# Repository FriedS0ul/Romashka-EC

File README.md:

Daisy40 compatible hybrid EC/MX pcb

My humble attempt to implement HE approach on a topre pcb(+mx cus why not)
Be aware that nothing out of here have been tested or have a firmare yet

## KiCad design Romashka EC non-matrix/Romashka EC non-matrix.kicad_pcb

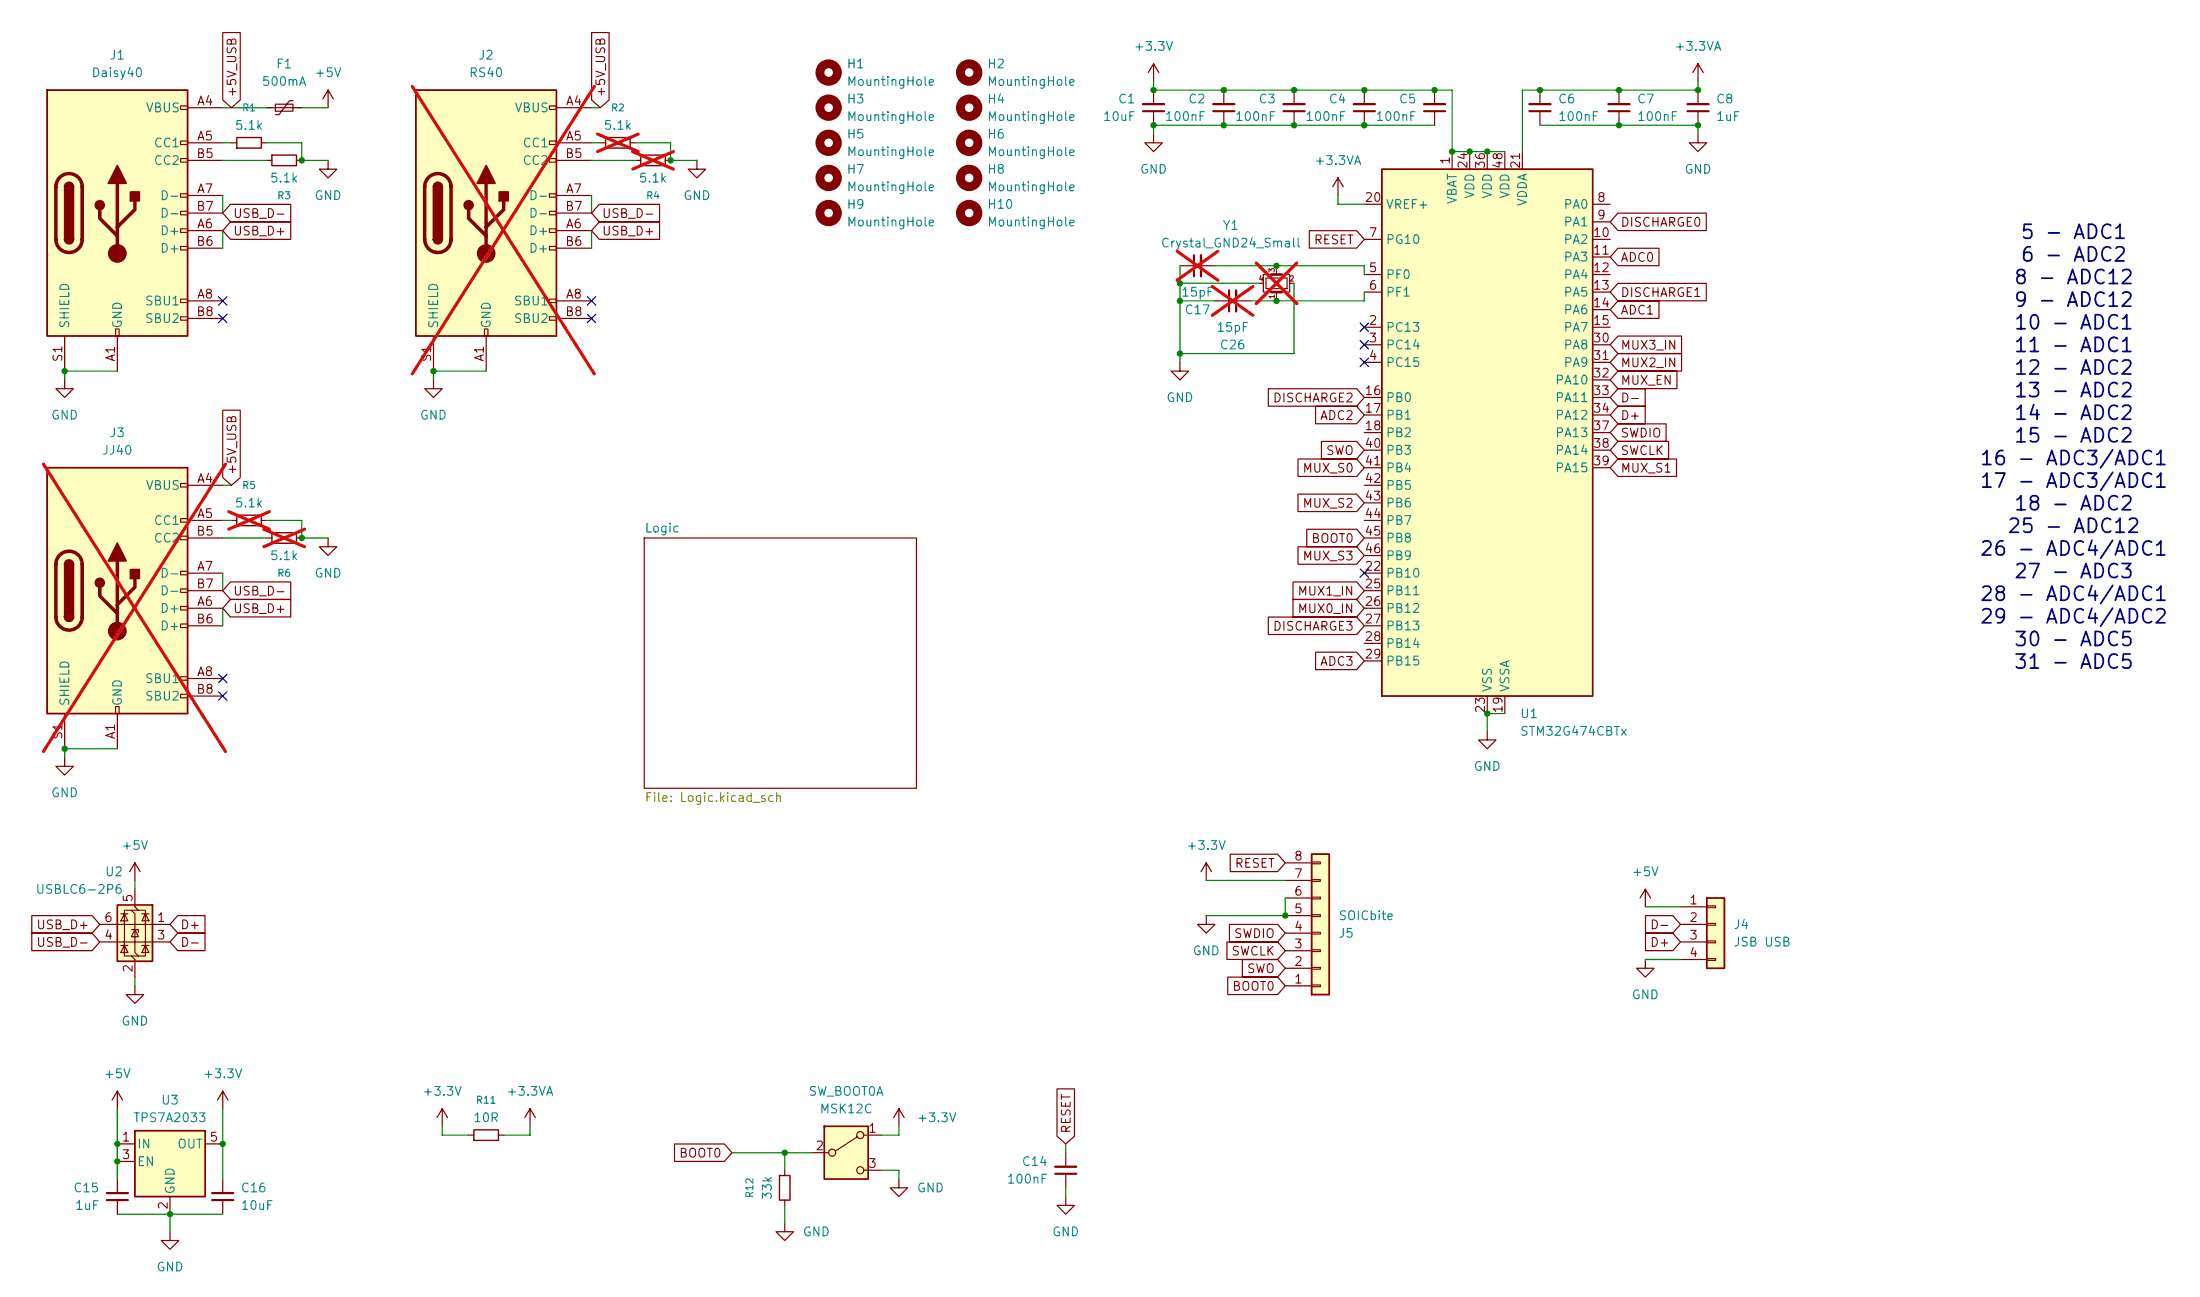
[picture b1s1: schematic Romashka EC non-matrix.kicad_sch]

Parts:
C1, C16: 10uF; C_0805_2012Metric
C2, C3, C4, C5, C6, C7, C14: 100nF; C_0402_1005Metric
C8, C15: 1uF; C_0603_1608Metric
C17, C26: 15pF; C_0402_1005Metric; not fitted
F1: 500mA; Fuse_0603_1608Metric
H1, H2, H3, H4, H5, H6, H7, H8, H9, H10: MountingHole; m2 hole
J1: Daisy40; USB_C_Receptacle_GCT_USB4105-xx-A_16P_TopMnt_Horizontal
J2: RS40; USB_C_Receptacle_GCT_USB4105-xx-A_16P_TopMnt_Horizontal; not fitted
J3: JJ40; USB_C_Receptacle_GCT_USB4105-xx-A_16P_TopMnt_Horizontal; not fitted
J4: JSB USB; JST_SH_SM04B-SRSS-TB_1x04-1MP_P1.00mm_Horizontal
J5: SOICbite; SOICbite_footprint
R1, R3: 5.1k; R_0603_1608Metric
R2, R4, R5, R6: 5.1k; R_0603_1608Metric; not fitted
R11: 10R; R_0603_1608Metric
R12: 33k; R_0603_1608Metric
SW_BOOT0: MSK12C; slider-msk12c
U1: STM32G474CBTx; LQFP-48_7x7mm_P0.5mm
U2: USBLC6-2P6; SOT-563
U3: TPS7A2033; SOT-23-5
Y1: Crystal_GND24_Small; Crystal_SMD_3225-4Pin_3.2x2.5mm; not fitted

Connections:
+3.3V: C1.2, C2.2, C3.2, C4.2, C5.2, C16.2, J5.7, R11.1, SW_BOOT0.1 (A), U1.1 (VBAT), U1.24 (VDD), U1.36 (VDD), U1.48 (VDD), U3.5 (OUT); also elsewhere on the board
+3.3VA: C6.2, C7.2, C8.2, R11.2, U1.20 (VREF+), U1.21 (VDDA)
+5V: C15.2, F1.2, J4.1, U2.5 (VBUS), U3.1 (IN), U3.3 (EN)
+5V_USB: F1.1, J1.A4 (VBUS), J1.A9 (VBUS), J1.B4 (VBUS), J1.B9 (VBUS), J2.A4 (VBUS), J2.A9 (VBUS), J2.B4 (VBUS), J2.B9 (VBUS), J3.A4 (VBUS), J3.A9 (VBUS), J3.B4 (VBUS), J3.B9 (VBUS)
ADC0: U1.11 (PA3); also elsewhere on the board
ADC1: U1.14 (PA6); also elsewhere on the board
ADC2: U1.17 (PB1); also elsewhere on the board
ADC3: U1.29 (PB15); also elsewhere on the board
BOOT0: J5.1, R12.1, SW_BOOT0.2 (B), U1.45 (PB8)
D+: J4.3, U1.34 (PA12), U2.1 (I/O1)
D-: J4.2, U1.33 (PA11), U2.3 (I/O2)
DISCHARGE0: U1.9 (PA1); also elsewhere on the board
DISCHARGE1: U1.13 (PA5); also elsewhere on the board
DISCHARGE2: U1.16 (PB0); also elsewhere on the board
DISCHARGE3: U1.27 (PB13); also elsewhere on the board
GND: C1.1, C2.1, C3.1, C4.1, C5.1, C6.1, C7.1, C8.1, C14.1, C15.1, C16.1, C17.1, C26.1, J1.A1 (GND), J1.A12 (GND), J1.B1 (GND), J1.B12 (GND), J1.S1 (SHIELD), J2.A1 (GND), J2.A12 (GND), J2.B1 (GND), J2.B12 (GND), J2.S1 (SHIELD), J3.A1 (GND), J3.A12 (GND), J3.B1 (GND), J3.B12 (GND), J3.S1 (SHIELD), J4.4, J5.5, J5.6, R1.2, R2.2, R3.2, R4.2, R5.2, R6.2, R12.2, SW_BOOT0.3 (C), U1.19 (VSSA), U1.23 (VSS), U1.35 (VSS), U1.47 (VSS), U2.2 (GND), U3.2 (GND), Y1.2, Y1.4; also elsewhere on the board
MUX0_IN: U1.26 (PB12); also elsewhere on the board
MUX1_IN: U1.25 (PB11); also elsewhere on the board
MUX2_IN: U1.31 (PA9); also elsewhere on the board
MUX3_IN: U1.30 (PA8); also elsewhere on the board
MUX_EN: U1.32 (PA10); also elsewhere on the board
MUX_S0: U1.41 (PB4); also elsewhere on the board
MUX_S1: U1.39 (PA15); also elsewhere on the board
MUX_S2: U1.43 (PB6); also elsewhere on the board
MUX_S3: U1.46 (PB9); also elsewhere on the board
unnamed: J1.A5 (CC1), R1.1
unnamed: J1.B5 (CC2), R3.1
unnamed: J2.A5 (CC1), R2.1
unnamed: J2.B5 (CC2), R4.1
unnamed: J3.A5 (CC1), R5.1
unnamed: J3.B5 (CC2), R6.1
unnamed: C17.2, U1.5 (PF0), Y1.3
unnamed: C26.2, U1.6 (PF1), Y1.1
RESET: C14.2, J5.8, U1.7 (PG10)
SWCLK: J5.3, U1.38 (PA14)
SWDIO: J5.4, U1.37 (PA13)
SWO: J5.2, U1.40 (PB3)
USB_D+: J1.A6 (D+), J1.B6 (D+), J2.A6 (D+), J2.B6 (D+), J3.A6 (D+), J3.B6 (D+), U2.6 (I/O1)
USB_D-: J1.A7 (D-), J1.B7 (D-), J2.A7 (D-), J2.B7 (D-), J3.A7 (D-), J3.B7 (D-), U2.4 (I/O2)

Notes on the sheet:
5 - ADC1 6 - ADC2 8 - ADC12 9 - ADC12 10 - ADC1 11 - ADC1 12 - ADC2 13 - ADC2 14 - ADC2 15 - ADC2 16 - ADC3/ADC1 17 - ADC3/ADC1 18 - ADC2 25 - ADC12 26 - ADC4/ADC1 27 - ADC3 28 - ADC4/ADC1 29 - ADC4/ADC2 30 - ADC5 31 - ADC5

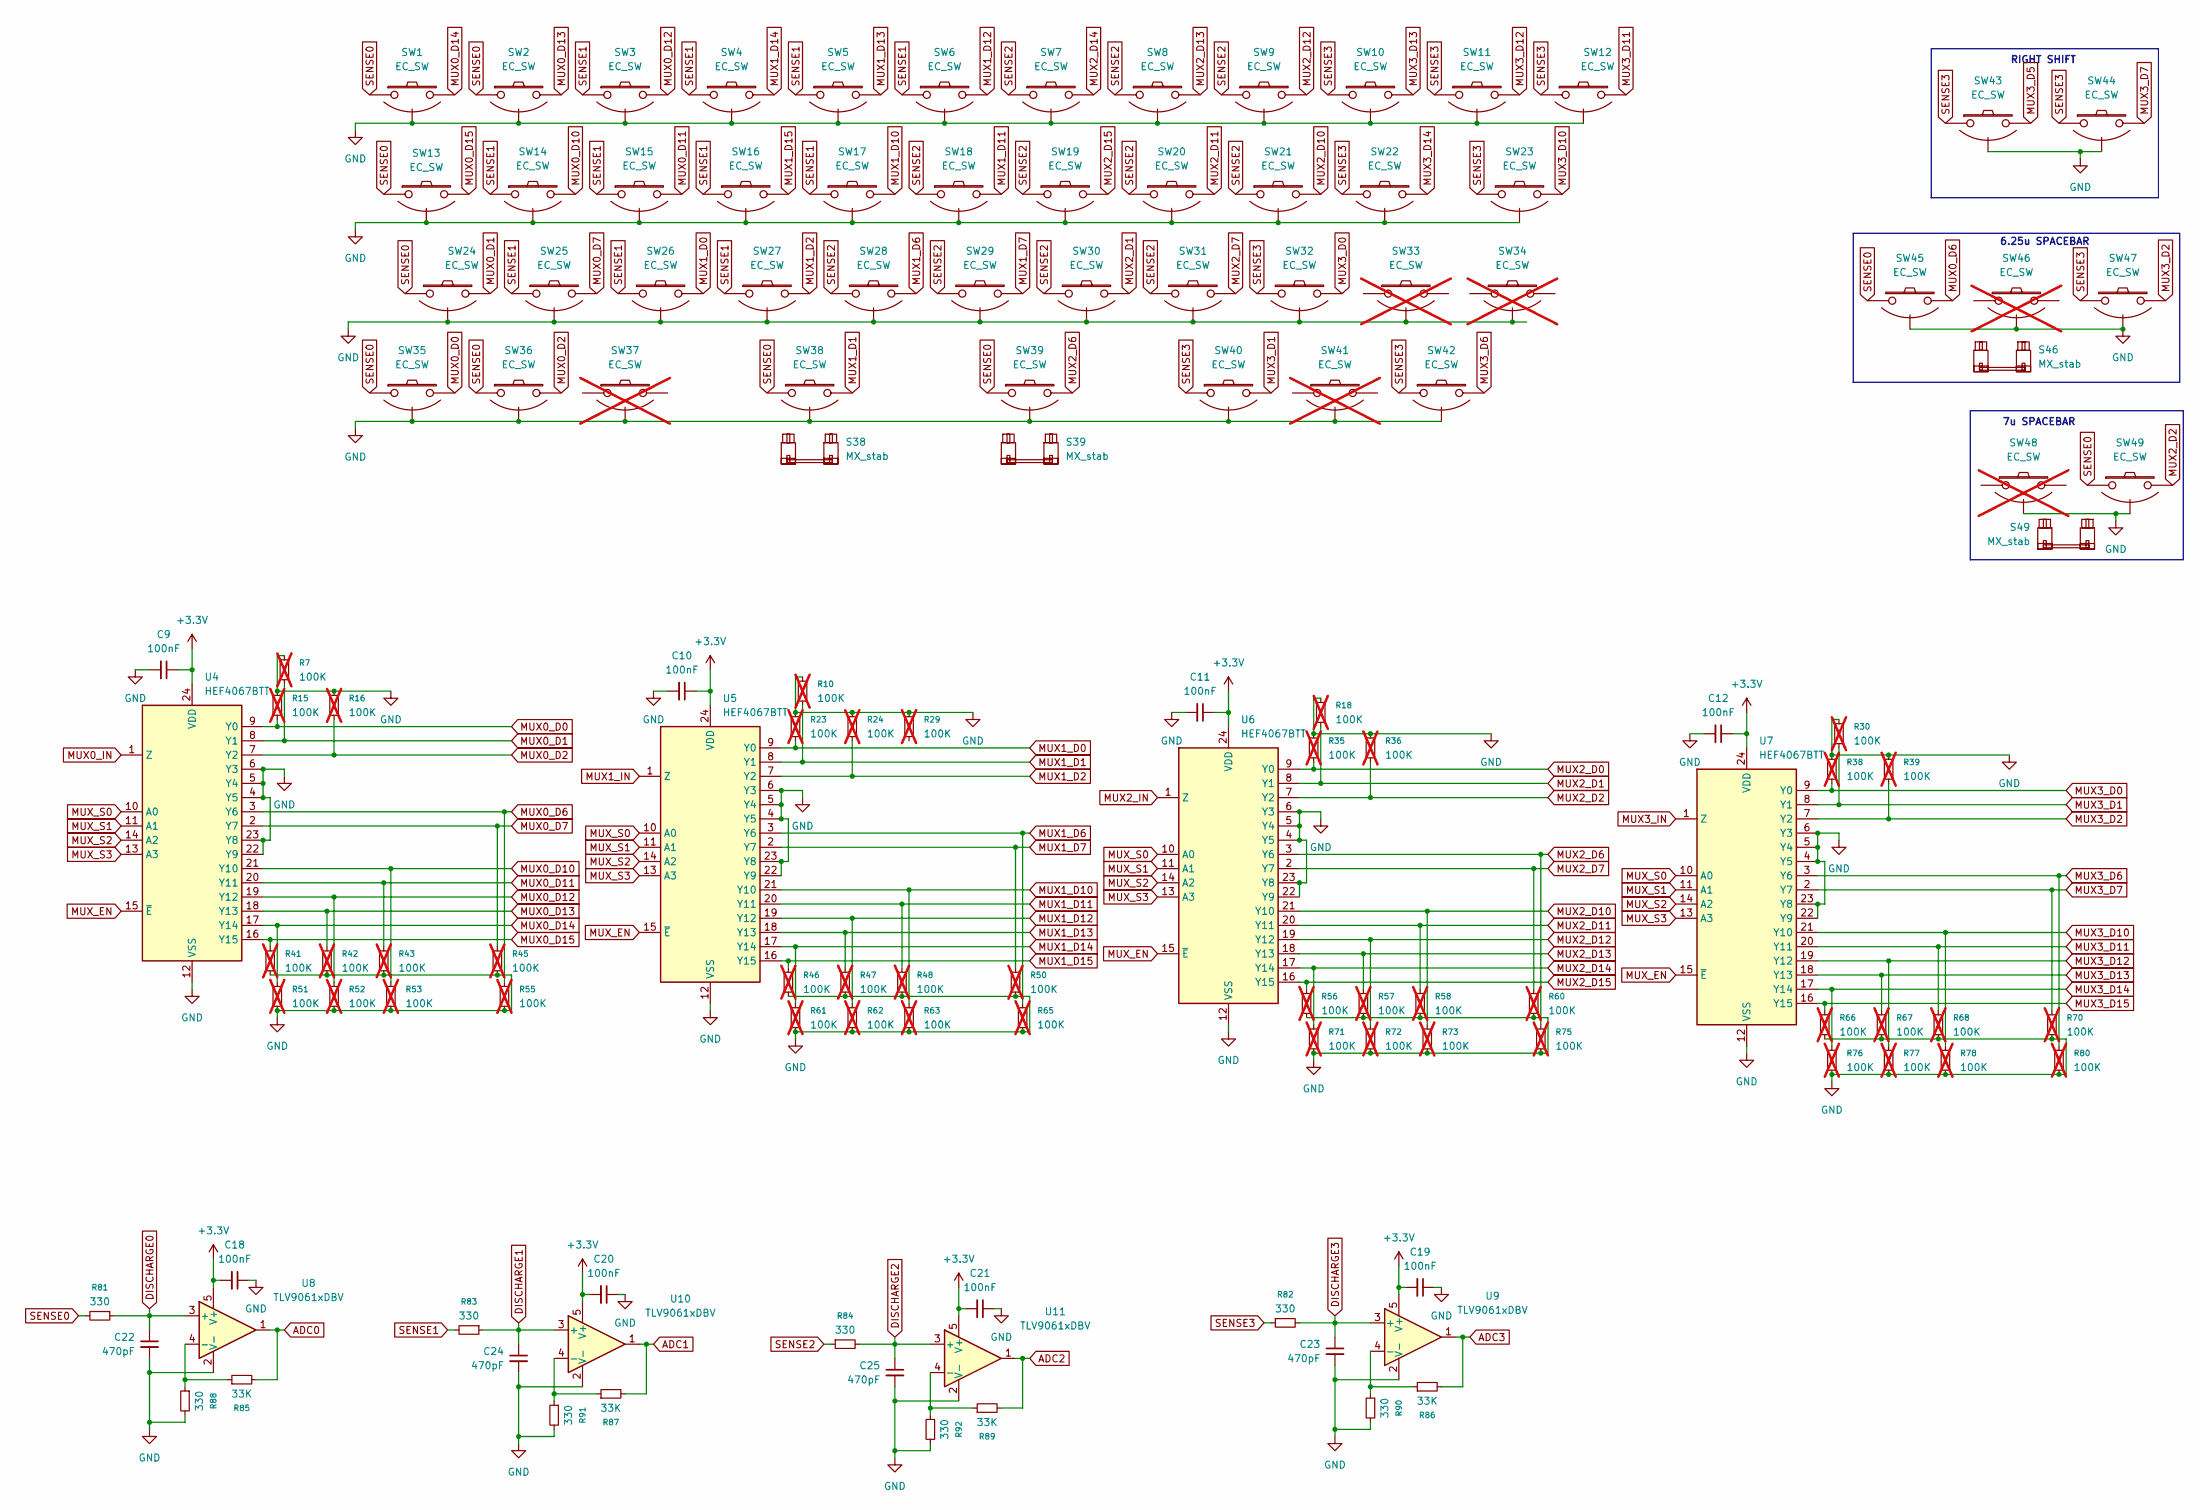
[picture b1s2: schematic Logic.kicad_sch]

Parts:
C9, C10, C11, C12, C18, C19, C20, C21: 100nF; C_0402_1005Metric
C22, C23, C24, C25: 470pF; C_0603_1608Metric
R7, R10, R15, R16, R18, R23, R24, R29, R30, R35, R36, R38, R39, R41, R42, R43, R45, R46, R47, R48, R50, R51, R52, R53, R55, R56, R57, R58, R60, R61, R62, R63, R65, R66, R67, R68, R70, R71, R72, R73, R75, R76, R77, R78, R80: 100K; R_0603_1608Metric; not fitted
R81, R82, R83, R84, R88, R90, R91, R92: 330; R_0603_1608Metric
R85, R86, R87, R89: 33K; R_0603_1608Metric
S38: MX_stab; STAB_MX_2.25u
S39: MX_stab; STAB_MX_2.75u
S46: MX_stab; STAB_MX_6.25u
S49: MX_stab; STAB_MX_7u
SW1, SW2, SW3, SW6, SW7, SW40, SW42: EC_SW; ecs_pad_1U_hybrid_hotswap_V3
SW4, SW5, SW8, SW9, SW10, SW11, SW12, SW13, SW14, SW15, SW16, SW17, SW18, SW19, SW20, SW21, SW22, SW23, SW24, SW25, SW26, SW27, SW28, SW29, SW30, SW31, SW32, SW35, SW38, SW39: EC_SW; ecs_pad_1U_hybrid_hotswap_V3_switched_sides
SW33, SW34, SW37, SW41, SW46, SW48: EC_SW; ecs_pad_1U_hybrid_hotswap_V3; not fitted
SW36, SW43, SW44, SW45, SW47: EC_SW; ecs_pad_hybrid_hotswap_2.381_V3
SW49: EC_SW; ecs_pad_hybrid_hotswap_7.144_V3
U4, U5, U6, U7: HEF4067BTT; TSSOP-24_4.4x7.8mm_P0.65mm
U8, U9, U10, U11: TLV9061xDBV; SOT-23-5

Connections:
+3.3V: C9.1, C10.1, C11.1, C12.1, C18.2, C19.2, C20.2, C21.2, U4.24 (VDD), U5.24 (VDD), U6.24 (VDD), U7.24 (VDD), U8.5 (V+), U9.5 (V+), U10.5 (V+), U11.5 (V+); also elsewhere on the board
ADC0: R85.2, U8.1; also elsewhere on the board
ADC1: R87.2, U10.1; also elsewhere on the board
ADC2: R89.2, U11.1; also elsewhere on the board
ADC3: R86.2, U9.1; also elsewhere on the board
DISCHARGE0: C22.1, R81.1, U8.3 (+); also elsewhere on the board
DISCHARGE1: C24.1, R83.1, U10.3 (+); also elsewhere on the board
DISCHARGE2: C25.1, R84.2, U11.3 (+); also elsewhere on the board
DISCHARGE3: C23.1, R82.2, U9.3 (+); also elsewhere on the board
GND: C9.2, C10.2, C11.2, C12.2, C18.1, C19.1, C20.1, C21.1, C22.2, C23.2, C24.2, C25.2, R7.1, R10.1, R15.1, R16.1, R18.1, R23.1, R24.1, R29.1, R30.1, R35.1, R36.1, R38.1, R39.1, R41.2, R42.2, R43.2, R45.2, R46.2, R47.2, R48.2, R50.2, R51.2, R52.2, R53.2, R55.2, R56.2, R57.2, R58.2, R60.2, R61.2, R62.2, R63.2, R65.2, R66.2, R67.2, R68.2, R70.2, R71.2, R72.2, R73.2, R75.2, R76.2, R77.2, R78.2, R80.2, R88.2, R90.2, R91.2, R92.2, SW1.3 (SG), SW2.3 (SG), SW3.3 (SG), SW4.3 (SG), SW5.3 (SG), SW6.3 (SG), SW7.3 (SG), SW8.3 (SG), SW9.3 (SG), SW10.3 (SG), SW11.3 (SG), SW12.3 (SG), SW13.3 (SG), SW14.3 (SG), SW15.3 (SG), SW16.3 (SG), SW17.3 (SG), SW18.3 (SG), SW19.3 (SG), SW20.3 (SG), SW21.3 (SG), SW22.3 (SG), SW23.3 (SG), SW24.3 (SG), SW25.3 (SG), SW26.3 (SG), SW27.3 (SG), SW28.3 (SG), SW29.3 (SG), SW30.3 (SG), SW31.3 (SG), SW32.3 (SG), SW33.3 (SG), SW34.3 (SG), SW35.3 (SG), SW36.3 (SG), SW37.3 (SG), SW38.3 (SG), SW39.3 (SG), SW40.3 (SG), SW41.3 (SG), SW42.3 (SG), SW43.3 (SG), SW44.3 (SG), SW45.3 (SG), SW46.3 (SG), SW47.3 (SG), SW48.3 (SG), SW49.3 (SG), U4.4 (Y5), U4.5 (Y4), U4.6 (Y3), U4.12 (VSS), U4.22 (Y9), U4.23 (Y8), U5.4 (Y5), U5.5 (Y4), U5.6 (Y3), U5.12 (VSS), U5.22 (Y9), U5.23 (Y8), U6.4 (Y5), U6.5 (Y4), U6.6 (Y3), U6.12 (VSS), U6.22 (Y9), U6.23 (Y8), U7.4 (Y5), U7.5 (Y4), U7.6 (Y3), U7.12 (VSS), U7.22 (Y9), U7.23 (Y8), U8.2 (V-), U9.2 (V-), U10.2 (V-), U11.2 (V-); also elsewhere on the board
MUX0_D0: R15.2, SW35.2, U4.9 (Y0)
MUX0_D1: R7.2, SW24.2, U4.8 (Y1)
MUX0_D2: R16.2, SW36.2, U4.7 (Y2)
MUX0_D6: R55.1, SW45.2, U4.3 (Y6)
MUX0_D7: R45.1, SW25.2, U4.2 (Y7)
MUX0_D10: R53.1, SW14.2, U4.21 (Y10)
MUX0_D11: R43.1, SW15.2, U4.20 (Y11)
MUX0_D12: R52.1, SW3.2, U4.19 (Y12)
MUX0_D13: R42.1, SW2.2, U4.18 (Y13)
MUX0_D14: R51.1, SW1.2, U4.17 (Y14)
MUX0_D15: R41.1, SW13.2, U4.16 (Y15)
MUX0_IN: U4.1 (Z); also elsewhere on the board
MUX1_D0: R23.2, SW26.2, U5.9 (Y0)
MUX1_D1: R10.2, SW38.2, U5.8 (Y1)
MUX1_D2: R24.2, SW27.2, U5.7 (Y2)
MUX1_D6: R65.1, SW28.2, U5.3 (Y6)
MUX1_D7: R50.1, SW29.2, U5.2 (Y7)
MUX1_D10: R63.1, SW17.2, U5.21 (Y10)
MUX1_D11: R48.1, SW18.2, U5.20 (Y11)
MUX1_D12: R62.1, SW6.2, U5.19 (Y12)
MUX1_D13: R47.1, SW5.2, U5.18 (Y13)
MUX1_D14: R61.1, SW4.2, U5.17 (Y14)
MUX1_D15: R46.1, SW16.2, U5.16 (Y15)
MUX1_IN: U5.1 (Z); also elsewhere on the board
MUX2_D0: R35.2, U6.9 (Y0)
MUX2_D1: R18.2, SW30.2, U6.8 (Y1)
MUX2_D2: R36.2, SW49.2, U6.7 (Y2)
MUX2_D6: R75.1, SW39.2, U6.3 (Y6)
MUX2_D7: R60.1, SW31.2, U6.2 (Y7)
MUX2_D10: R73.1, SW21.2, U6.21 (Y10)
MUX2_D11: R58.1, SW20.2, U6.20 (Y11)
MUX2_D12: R72.1, SW9.2, U6.19 (Y12)
MUX2_D13: R57.1, SW8.2, U6.18 (Y13)
MUX2_D14: R71.1, SW7.2, U6.17 (Y14)
MUX2_D15: R56.1, SW19.2, U6.16 (Y15)
MUX2_IN: U6.1 (Z); also elsewhere on the board
MUX3_D0: R38.2, SW32.2, U7.9 (Y0)
MUX3_D1: R30.2, SW40.2, U7.8 (Y1)
MUX3_D2: R39.2, SW47.2, U7.7 (Y2)
MUX3_D5: SW43.2
MUX3_D6: R80.1, SW42.2, U7.3 (Y6)
MUX3_D7: R70.1, SW44.2, U7.2 (Y7)
MUX3_D10: R78.1, SW23.2, U7.21 (Y10)
MUX3_D11: R68.1, SW12.2, U7.20 (Y11)
MUX3_D12: R77.1, SW11.2, U7.19 (Y12)
MUX3_D13: R67.1, SW10.2, U7.18 (Y13)
MUX3_D14: R76.1, SW22.2, U7.17 (Y14)
MUX3_D15: R66.1, U7.16 (Y15)
MUX3_IN: U7.1 (Z); also elsewhere on the board
MUX_EN: U4.15 (~E), U5.15 (~E), U6.15 (~E), U7.15 (~E); also elsewhere on the board
MUX_S0: U4.10 (A0), U5.10 (A0), U6.10 (A0), U7.10 (A0); also elsewhere on the board
MUX_S1: U4.11 (A1), U5.11 (A1), U6.11 (A1), U7.11 (A1); also elsewhere on the board
MUX_S2: U4.14 (A2), U5.14 (A2), U6.14 (A2), U7.14 (A2); also elsewhere on the board
MUX_S3: U4.13 (A3), U5.13 (A3), U6.13 (A3), U7.13 (A3); also elsewhere on the board
unnamed: R85.1, R88.1, U8.4 (-)
unnamed: R86.1, R90.1, U9.4 (-)
unnamed: R87.1, R91.1, U10.4 (-)
unnamed: R89.1, R92.1, U11.4 (-)
SENSE0: R81.2, SW1.1, SW2.1, SW13.1, SW24.1, SW35.1, SW36.1, SW38.1, SW39.1, SW45.1, SW49.1
SENSE1: R83.2, SW3.1, SW4.1, SW5.1, SW6.1, SW14.1, SW15.1, SW16.1, SW17.1, SW25.1, SW26.1, SW27.1
SENSE2: R84.1, SW7.1, SW8.1, SW9.1, SW18.1, SW19.1, SW20.1, SW21.1, SW28.1, SW29.1, SW30.1, SW31.1
SENSE3: R82.1, SW10.1, SW11.1, SW12.1, SW22.1, SW23.1, SW32.1, SW40.1, SW42.1, SW43.1, SW44.1, SW47.1

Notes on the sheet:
7u SPACEBAR
6.25u SPACEBAR
RIGHT SHIFT

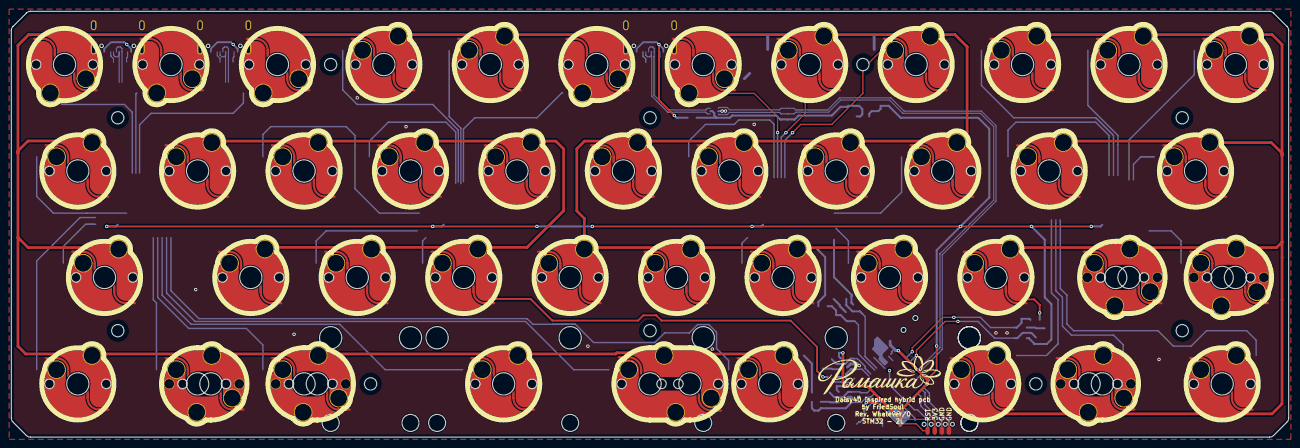
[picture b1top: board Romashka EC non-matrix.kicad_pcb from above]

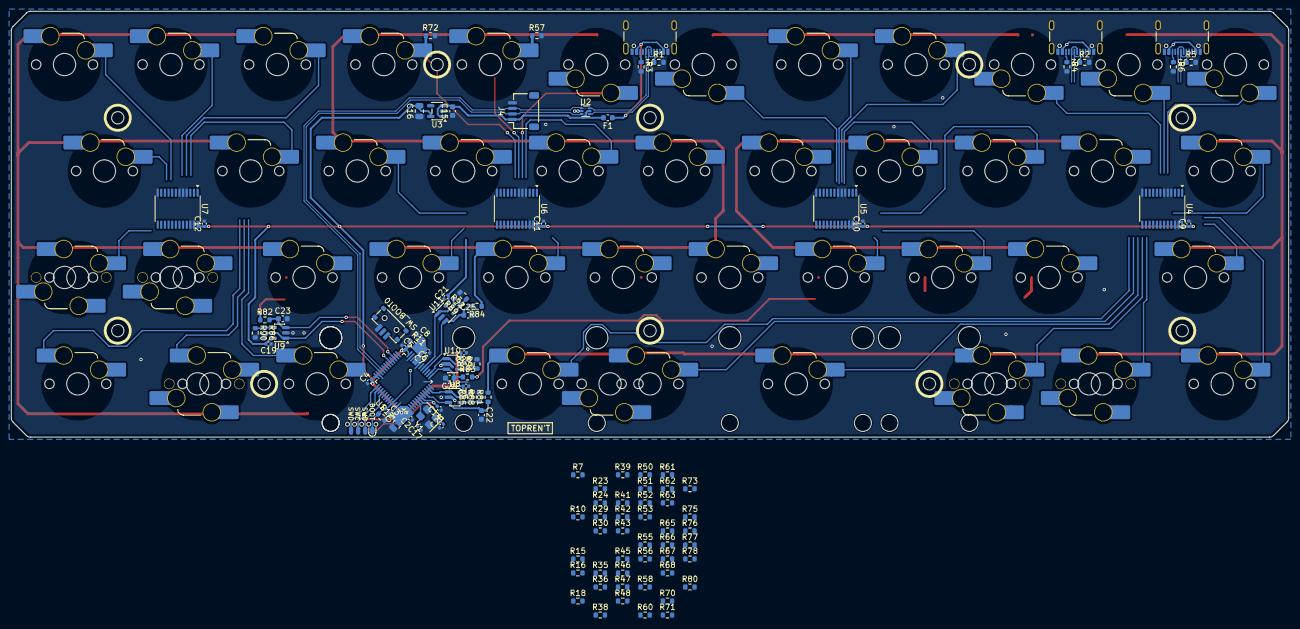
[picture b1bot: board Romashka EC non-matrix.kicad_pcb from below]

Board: 2 copper layers, 228.6 x 76.2 mm, 166 parts (109 on the bottom side), 91 nets.

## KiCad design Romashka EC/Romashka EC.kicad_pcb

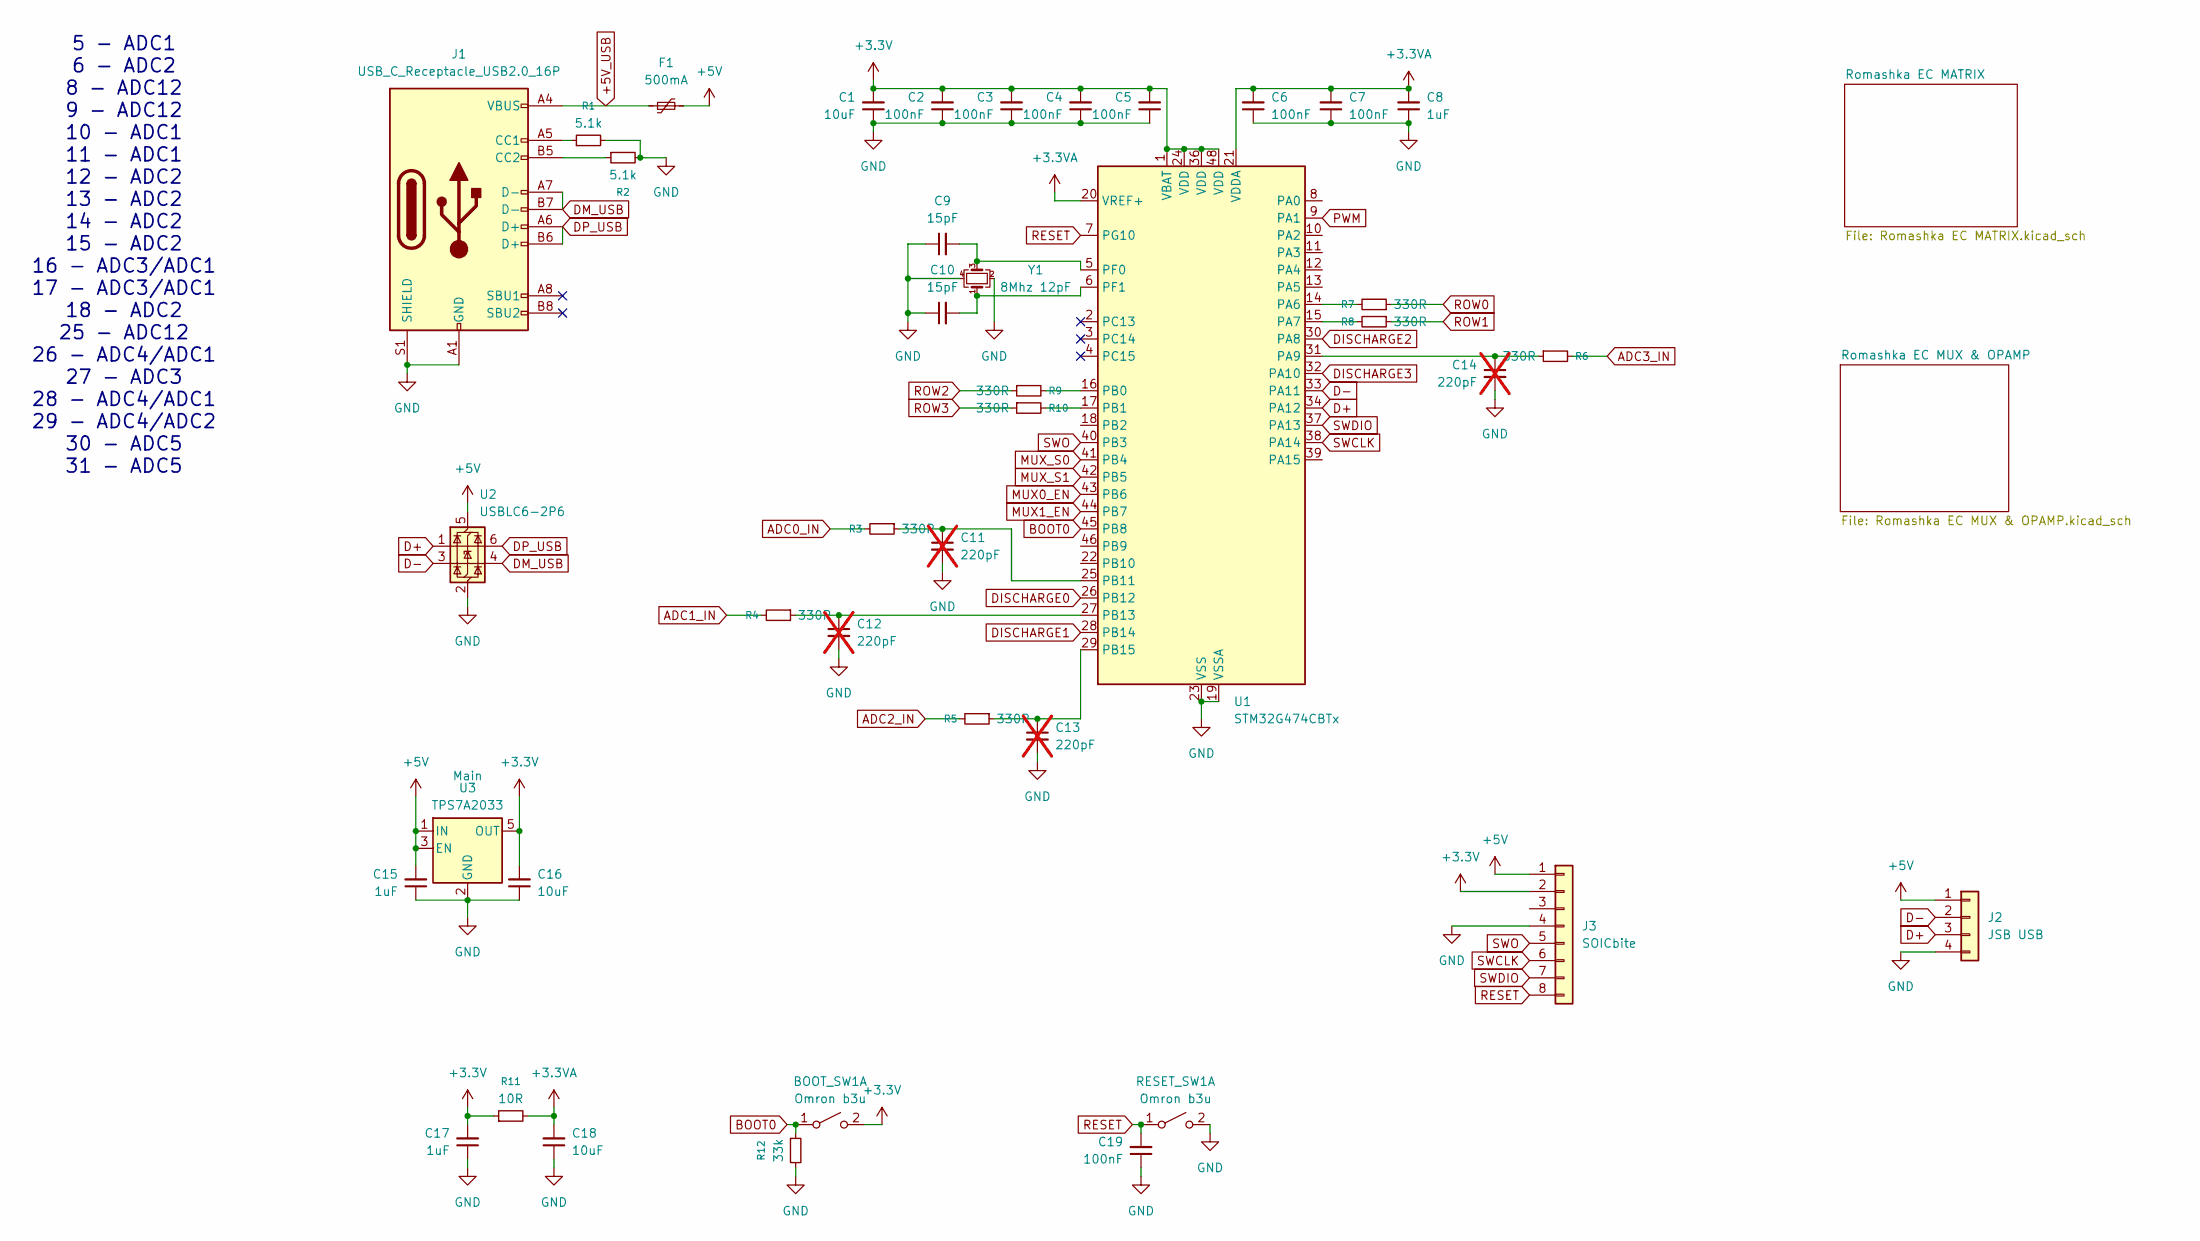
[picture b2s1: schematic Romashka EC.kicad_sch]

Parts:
BOOT_SW1: Omron b3u; SW_SPST_B3U-1000P
C1, C16, C18: 10uF; C_0805_2012Metric
C2, C3, C4, C5, C6, C7, C19: 100nF; C_0402_1005Metric
C8, C15, C17: 1uF; C_0603_1608Metric
C9, C10: 15pF; C_0402_1005Metric
C11, C12, C13, C14: 220pF; C_0603_1608Metric; not fitted
F1: 500mA; Fuse_0603_1608Metric
J1: USB_C_Receptacle_USB2.0_16P; USB_C_Receptacle_GCT_USB4105-xx-A_16P_TopMnt_Horizontal
J2: JSB USB; JST_SH_SM04B-SRSS-TB_1x04-1MP_P1.00mm_Horizontal
J3: SOICbite; SOICbite_footprint
R1, R2: 5.1k; R_0603_1608Metric
R3, R4, R5, R6, R7, R8, R9, R10: 330R; R_0603_1608Metric
R11: 10R; R_0603_1608Metric
R12: 33k; R_0603_1608Metric
RESET_SW1: Omron b3u; SW_SPST_B3U-1000P
U1: STM32G474CBTx; LQFP-48_7x7mm_P0.5mm
U2: USBLC6-2P6; SOT-563
U3: TPS7A2033; SOT-23-5
Y1: 8Mhz 12pF; Crystal_SMD_3225-4Pin_3.2x2.5mm

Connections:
+3.3V: BOOT_SW1.2 (B), C1.2, C2.2, C3.2, C4.2, C5.2, C16.2, C17.2, J3.2, R11.1, U1.1 (VBAT), U1.24 (VDD), U1.36 (VDD), U1.48 (VDD), U3.5 (OUT); also elsewhere on the board
+3.3VA: C6.2, C7.2, C8.2, C18.2, R11.2, U1.20 (VREF+), U1.21 (VDDA)
+5V: C15.2, F1.2, J2.1, J3.1, U2.5 (VBUS), U3.1 (IN), U3.3 (EN); also elsewhere on the board
+5V_USB: F1.1, J1.A4 (VBUS), J1.A9 (VBUS), J1.B4 (VBUS), J1.B9 (VBUS)
ADC0_IN: R3.2; also elsewhere on the board
ADC1_IN: R4.2; also elsewhere on the board
ADC2_IN: R5.2; also elsewhere on the board
ADC3_IN: R6.2; also elsewhere on the board
BOOT0: BOOT_SW1.1 (A), R12.1, U1.45 (PB8)
D+: J2.3, U1.34 (PA12), U2.1 (I/O1)
D-: J2.2, U1.33 (PA11), U2.3 (I/O2)
DISCHARGE0: U1.26 (PB12); also elsewhere on the board
DISCHARGE1: U1.28 (PB14); also elsewhere on the board
DISCHARGE2: U1.30 (PA8); also elsewhere on the board
DISCHARGE3: U1.32 (PA10); also elsewhere on the board
DM_USB: J1.A7 (D-), J1.B7 (D-), U2.4 (I/O2)
DP_USB: J1.A6 (D+), J1.B6 (D+), U2.6 (I/O1)
GND: C1.1, C2.1, C3.1, C4.1, C5.1, C6.1, C7.1, C8.1, C9.1, C10.1, C11.2, C12.2, C13.2, C14.2, C15.1, C16.1, C17.1, C18.1, C19.1, J1.A1 (GND), J1.A12 (GND), J1.B1 (GND), J1.B12 (GND), J1.S1 (SHIELD), J2.4, J3.4, R1.2, R2.2, R12.2, RESET_SW1.2 (B), U1.19 (VSSA), U1.23 (VSS), U1.35 (VSS), U1.47 (VSS), U2.2 (GND), U3.2 (GND), Y1.2, Y1.4; also elsewhere on the board
MUX0_EN: U1.43 (PB6); also elsewhere on the board
MUX1_EN: U1.44 (PB7); also elsewhere on the board
MUX_S0: U1.41 (PB4); also elsewhere on the board
MUX_S1: U1.42 (PB5); also elsewhere on the board
unnamed: J1.A5 (CC1), R1.1
unnamed: J1.B5 (CC2), R2.1
unnamed: R7.2, U1.14 (PA6)
unnamed: R8.2, U1.15 (PA7)
unnamed: C14.1, R6.1, U1.31 (PA9)
unnamed: R9.2, U1.16 (PB0)
unnamed: R10.2, U1.17 (PB1)
unnamed: C11.1, R3.1, U1.25 (PB11)
unnamed: C12.1, R4.1, U1.27 (PB13)
unnamed: C13.1, R5.1, U1.29 (PB15)
unnamed: C9.2, U1.5 (PF0), Y1.3
unnamed: C10.2, U1.6 (PF1), Y1.1
PWM: U1.9 (PA1)
RESET: C19.2, J3.8, RESET_SW1.1 (A), U1.7 (PG10)
ROW0: R7.1; also elsewhere on the board
ROW1: R8.1; also elsewhere on the board
ROW2: R9.1; also elsewhere on the board
ROW3: R10.1; also elsewhere on the board
SWCLK: J3.6, U1.38 (PA14)
SWDIO: J3.7, U1.37 (PA13)
SWO: J3.5, U1.40 (PB3)

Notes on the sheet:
5 - ADC1 6 - ADC2 8 - ADC12 9 - ADC12 10 - ADC1 11 - ADC1 12 - ADC2 13 - ADC2 14 - ADC2 15 - ADC2 16 - ADC3/ADC1 17 - ADC3/ADC1 18 - ADC2 25 - ADC12 26 - ADC4/ADC1 27 - ADC3 28 - ADC4/ADC1 29 - ADC4/ADC2 30 - ADC5 31 - ADC5

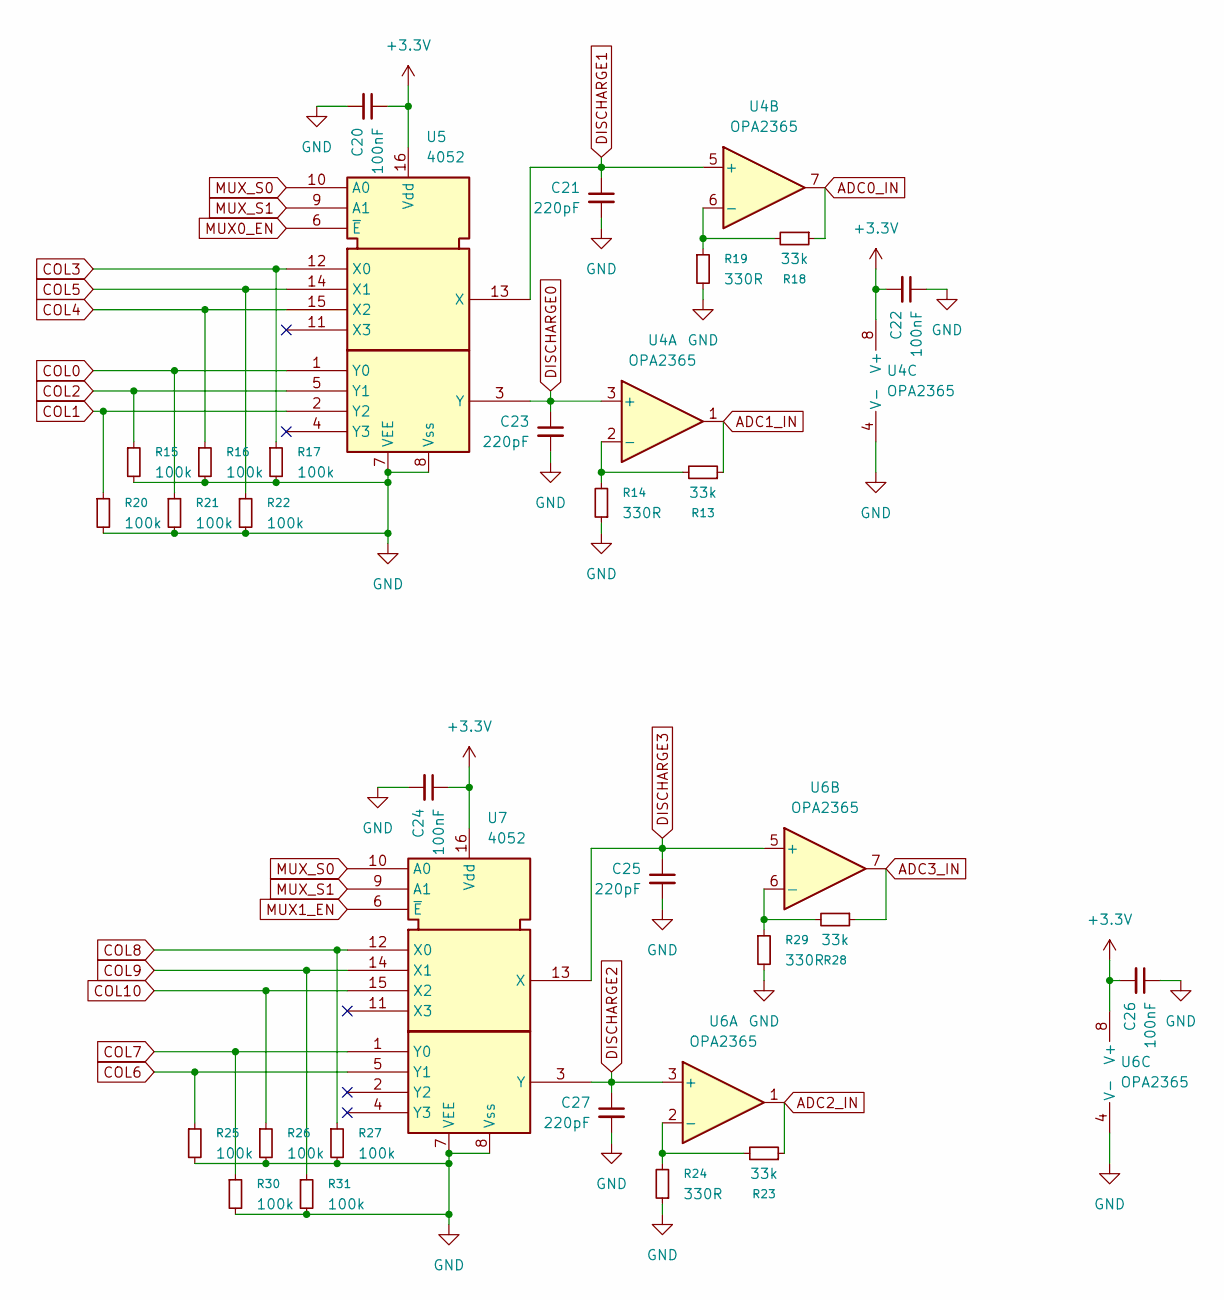
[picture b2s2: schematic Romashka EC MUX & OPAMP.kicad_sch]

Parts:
C20, C22, C24, C26: 100nF; C_0402_1005Metric
C21, C23, C25, C27: 220pF; C_0603_1608Metric
R13, R18, R23, R28: 33k; R_0603_1608Metric
R14, R19, R24, R29: 330R; R_0603_1608Metric
R15, R16, R17, R20, R21, R22, R25, R26, R27, R30, R31: 100k; R_0805_2012Metric
U4, U6: OPA2365; SOIC-8_3.9x4.9mm_P1.27mm
U5, U7: 4052; TSSOP-16_4.4x5mm_P0.65mm

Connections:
+3.3V: C20.1, C22.2, C24.1, C26.2, U4.8 (V+), U5.16 (Vdd), U6.8 (V+), U7.16 (Vdd); also elsewhere on the board
ADC0_IN: R18.1, U4.7; also elsewhere on the board
ADC1_IN: R13.1, U4.1; also elsewhere on the board
ADC2_IN: R23.1, U6.1; also elsewhere on the board
ADC3_IN: R28.1, U6.7; also elsewhere on the board
COL0: R21.1, U5.1 (Y0); also elsewhere on the board
COL1: R20.1, U5.2 (Y2); also elsewhere on the board
COL2: R15.1, U5.5 (Y1); also elsewhere on the board
COL3: R17.1, U5.12 (X0); also elsewhere on the board
COL4: R16.1, U5.15 (X2); also elsewhere on the board
COL5: R22.1, U5.14 (X1); also elsewhere on the board
COL6: R25.1, U7.5 (Y1); also elsewhere on the board
COL7: R30.1, U7.1 (Y0); also elsewhere on the board
COL8: R27.1, U7.12 (X0); also elsewhere on the board
COL9: R31.1, U7.14 (X1); also elsewhere on the board
COL10: R26.1, U7.15 (X2); also elsewhere on the board
DISCHARGE0: C23.1, U4.3 (+), U5.3 (Y); also elsewhere on the board
DISCHARGE1: C21.1, U4.5 (+), U5.13 (X); also elsewhere on the board
DISCHARGE2: C27.1, U6.3 (+), U7.3 (Y); also elsewhere on the board
DISCHARGE3: C25.1, U6.5 (+), U7.13 (X); also elsewhere on the board
GND: C20.2, C21.2, C22.1, C23.2, C24.2, C25.2, C26.1, C27.2, R14.1, R15.2, R16.2, R17.2, R19.2, R20.2, R21.2, R22.2, R24.1, R25.2, R26.2, R27.2, R29.2, R30.2, R31.2, U4.4 (V-), U5.7 (VEE), U5.8 (Vss), U6.4 (V-), U7.7 (VEE), U7.8 (Vss); also elsewhere on the board
MUX0_EN: U5.6 (~E); also elsewhere on the board
MUX1_EN: U7.6 (~E); also elsewhere on the board
MUX_S0: U5.10 (A0), U7.10 (A0); also elsewhere on the board
MUX_S1: U5.9 (A1), U7.9 (A1); also elsewhere on the board
unnamed: R13.2, R14.2, U4.2 (-)
unnamed: R18.2, R19.1, U4.6 (-)
unnamed: R23.2, R24.2, U6.2 (-)
unnamed: R28.2, R29.1, U6.6 (-)
